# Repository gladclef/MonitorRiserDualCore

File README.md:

# Neopixel-Monitor-Riser-ESP32
A controller with several patterns of light that fits underneith my monitor riser. The goal was to maintain a simple interface that will eventually result in a nice clean setup.

It uses the two cores on the ESP32 to monitor a rotary encoder and manage the neopixel lights. The original project which used two arduinos to accomplish this task is at https://github.com/gladclef/NeoPixel-Monitor-Riser.

## Explainer Video

## I designed a PCB board!

## Parts
* adafruit things: http://www.adafruit.com/wishlists/489413
* 330 ohm resistors: https://www.sparkfun.com/products/11507
* 1000uF capacitors: https://www.digikey.com/product-detail/en/panasonic-electronic-components/6SEPC1000MD/P122181-ND/7105108
* pcb board: https://oshpark.com/shared_projects/wfCmhDWu

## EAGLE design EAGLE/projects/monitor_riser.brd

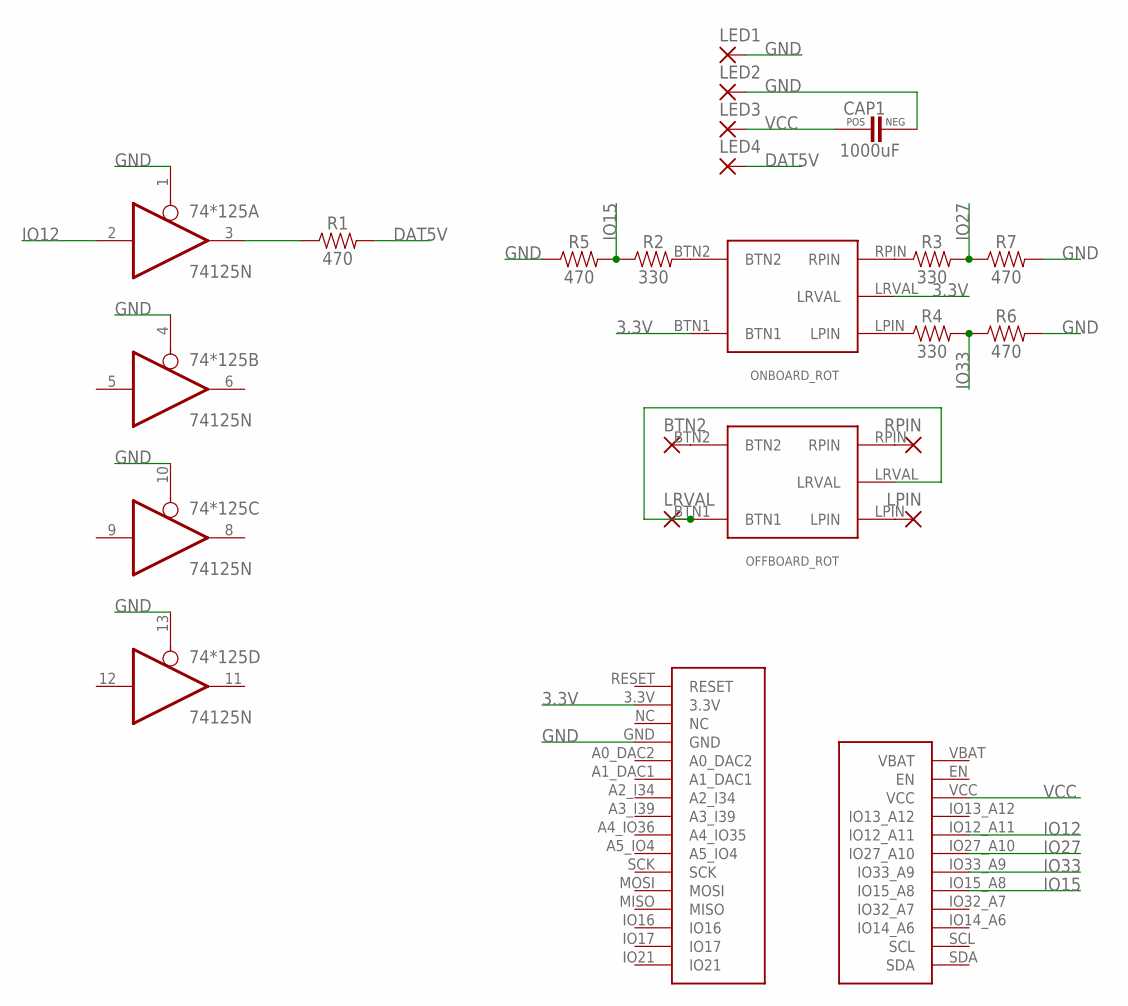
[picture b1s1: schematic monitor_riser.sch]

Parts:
74*125: 74125N; DIL14
BTN2: 1,6/0,9
CAP1: 1000uF; CAP1000UF_0807_0304
LED1, LED2, LED3, LED4: 1,6/0,9
LPIN: 1,6/0,9
LRVAL: 1,6/0,9
OFFBOARD_ROT: ROTARYENCODER
ONBOARD_ROT: ROTARYENCODER
R1, R5, R6, R7: 470; AXIAL-0.3
R2, R3, R4: 330; AXIAL-0.3
RPIN: 1,6/0,9
U$1: FEATHER32

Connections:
3.3V: ONBOARD_ROT.BTN1, ONBOARD_ROT.LRVAL, U$1.3.3V
DAT5V: LED4.1, R1.P$2 (2)
GND: 74*125.1 (OE), 74*125.4 (OE), 74*125.7 (GND), 74*125.10 (OE), 74*125.13 (OE), CAP1.NEG, LED1.1, LED2.1, R5.P$1 (1), R6.P$2 (2), R7.P$2 (2), U$1.GND
IO12: 74*125.2 (I), U$1.IO12_A11
IO15: R2.P$1 (1), R5.P$2 (2), U$1.IO15_A8
IO27: R3.P$2 (2), R7.P$1 (1), U$1.IO27_A10
IO33: R4.P$2 (2), R6.P$1 (1), U$1.IO33_A9
unnamed: 74*125.3 (O), R1.P$1 (1)
unnamed: ONBOARD_ROT.BTN2, R2.P$2 (2)
unnamed: ONBOARD_ROT.RPIN, R3.P$1 (1)
unnamed: ONBOARD_ROT.LPIN, R4.P$1 (1)
unnamed: LRVAL.1, OFFBOARD_ROT.BTN1, OFFBOARD_ROT.LRVAL
unnamed: BTN2.1, OFFBOARD_ROT.BTN2
unnamed: LPIN.1, OFFBOARD_ROT.LPIN
unnamed: OFFBOARD_ROT.RPIN, RPIN.1
VCC: 74*125.14 (VCC), CAP1.POS, LED3.1, U$1.VCC

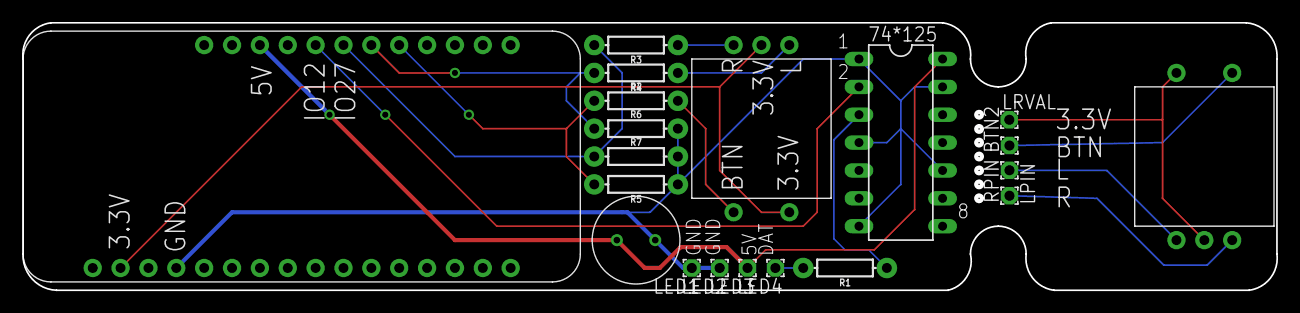
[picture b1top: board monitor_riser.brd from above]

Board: 2 copper layers, 114.1 x 24.2 mm, 20 parts (0 on the bottom side), 16 nets.

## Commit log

2019-04-07 added code and readme
2019-07-01 added board, images, and hardware list

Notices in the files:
parts and their libraries:
SparkFun-Resistors: Licensing: Creative Commons ShareAlike 4.0 International - https://creativecommons.org/licenses/by-sa/4.0
